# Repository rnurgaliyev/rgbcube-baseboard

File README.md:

# rgbcube-baseboard
BaseBoard design for RGB Cube Project

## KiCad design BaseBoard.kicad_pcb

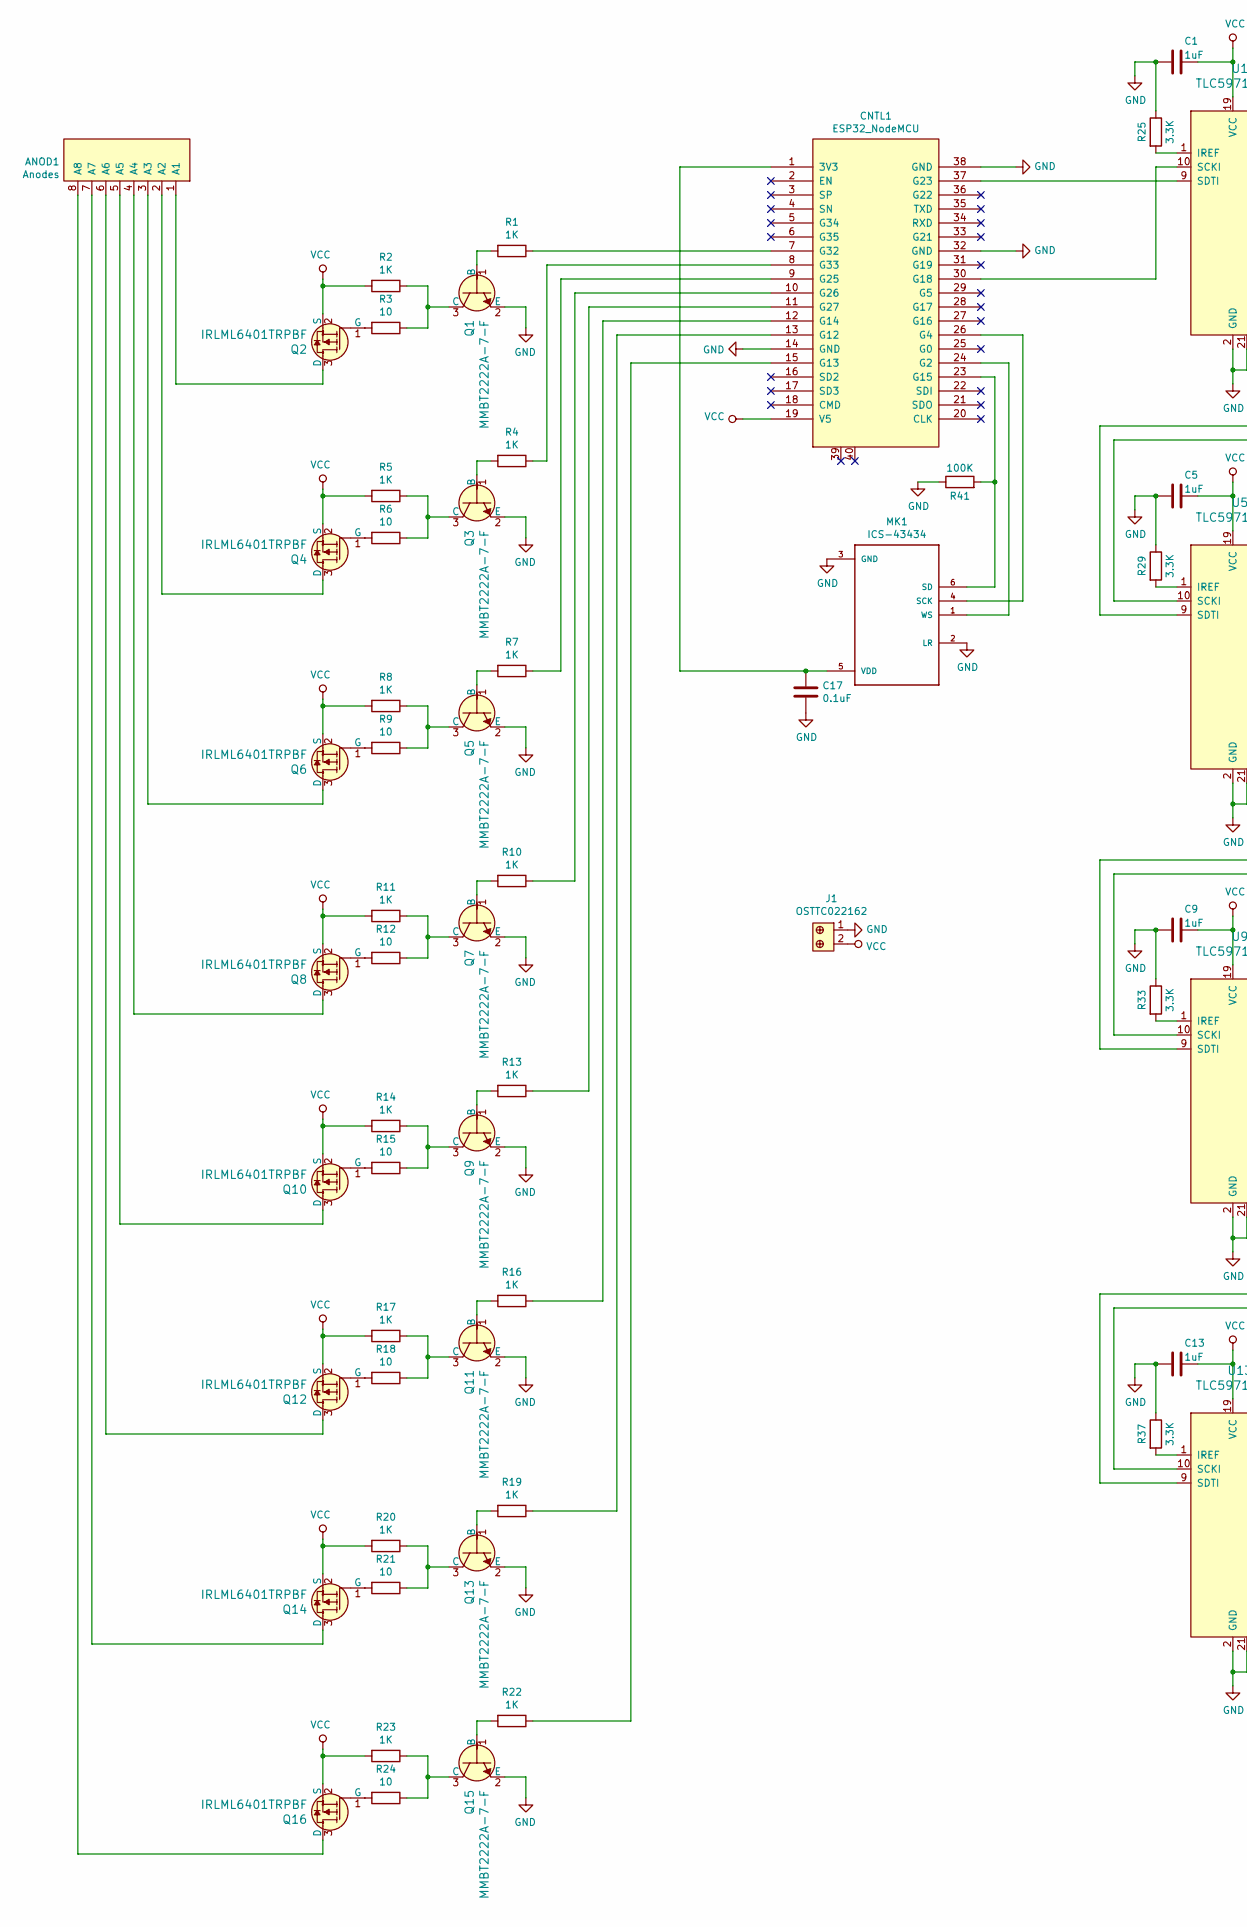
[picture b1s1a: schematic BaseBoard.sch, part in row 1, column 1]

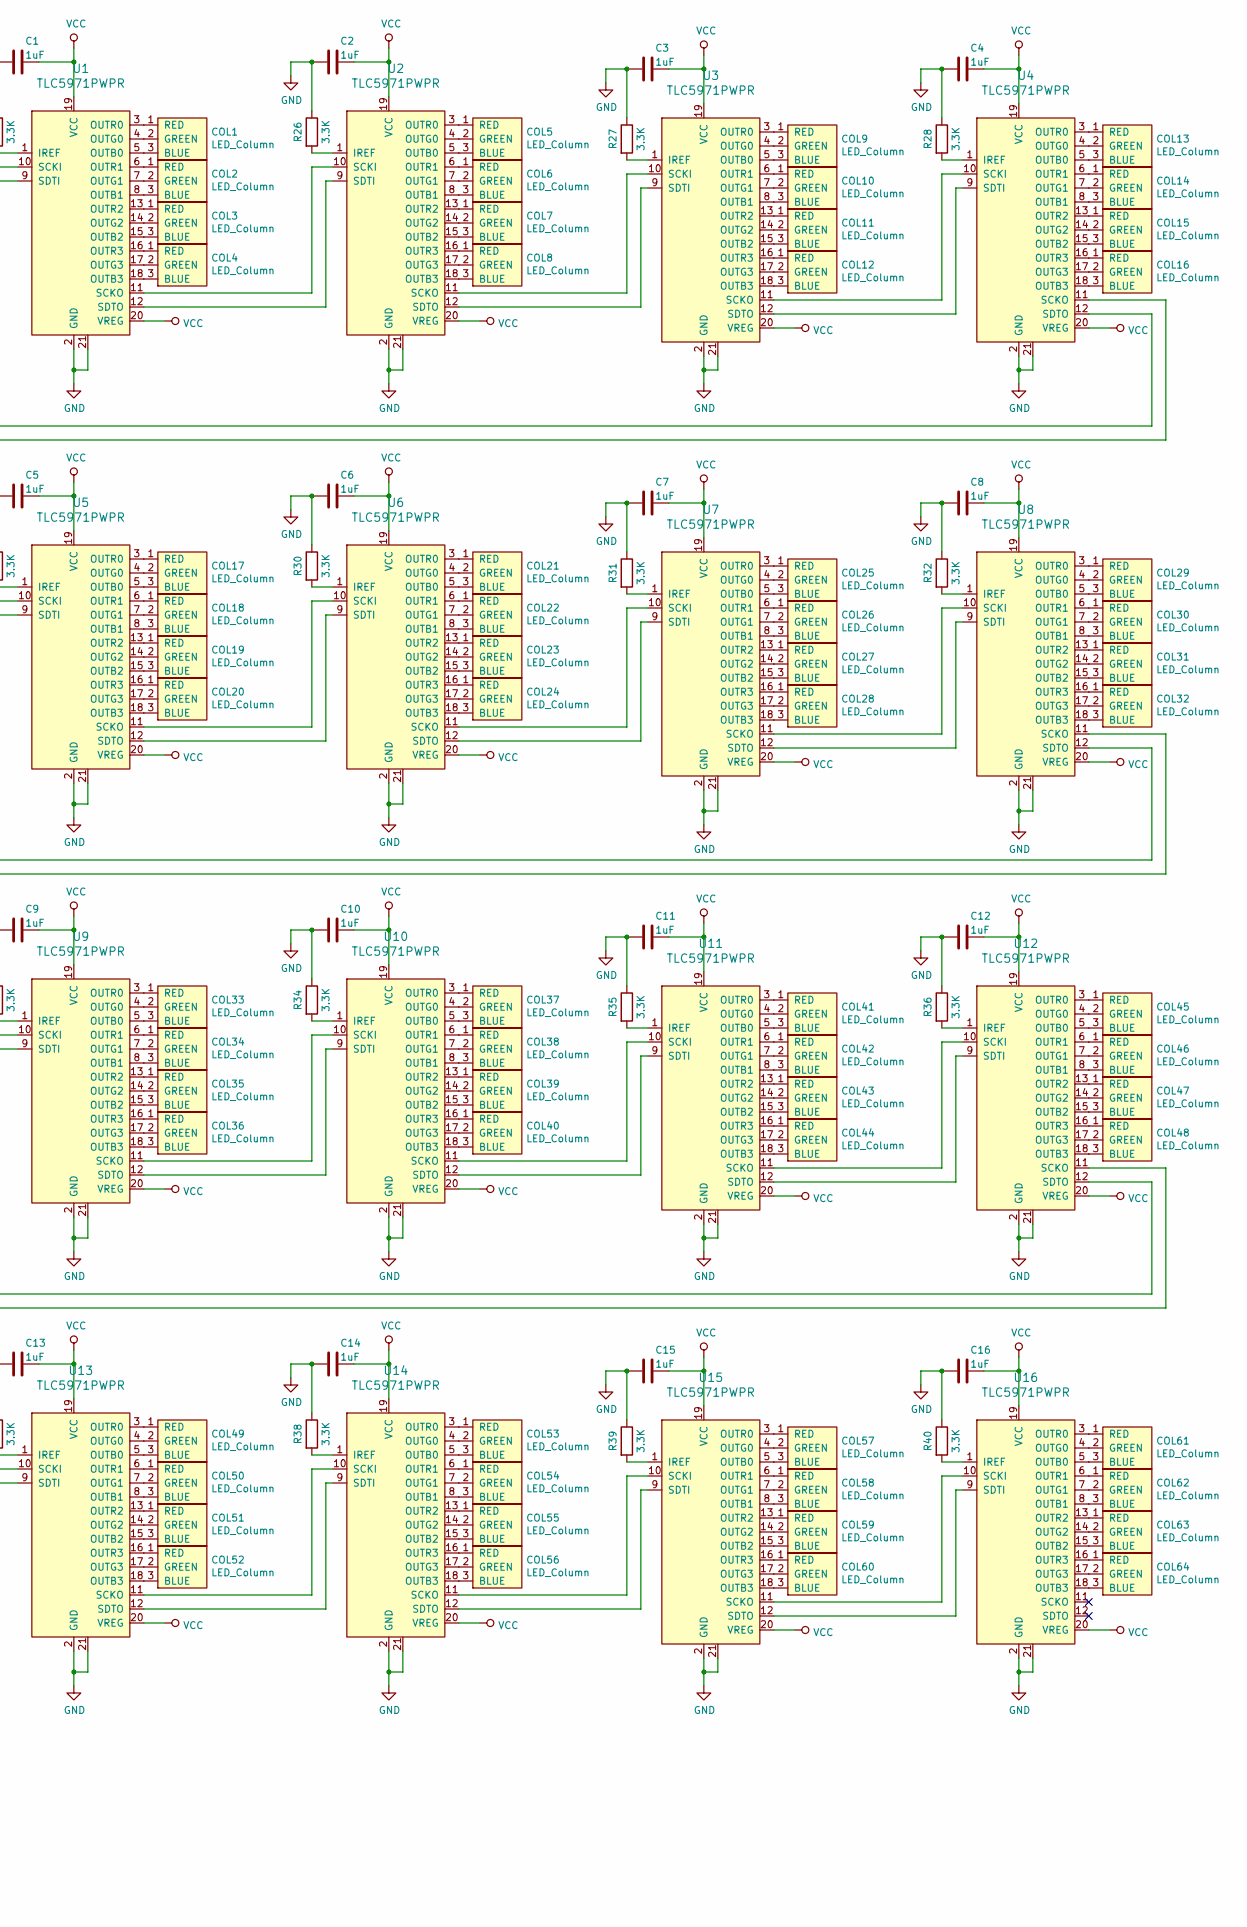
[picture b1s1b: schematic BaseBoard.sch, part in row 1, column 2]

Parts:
ANOD1: Anodes
C1, C2, C3, C4, C5, C6, C7, C8, C9, C10, C11, C12, C13, C14, C15, C16: 1uF; C_0805_2012Metric_Pad1.15x1.40mm_HandSolder
C17: 0.1uF; C_0805_2012Metric_Pad1.15x1.40mm_HandSolder
CNTL1: ESP32_NodeMCU
COL1, COL2, COL3, COL4, COL5, COL6, COL7, COL8, COL9, COL10, COL11, COL12, COL13, COL14, COL15, COL16, COL17, COL18, COL19, COL20, COL21, COL22, COL23, COL24, COL25, COL26, COL27, COL28, COL29, COL30, COL31, COL32, COL33, COL34, COL35, COL36, COL37, COL38, COL39, COL40, COL41, COL42, COL43, COL44, COL45, COL46, COL47, COL48, COL49, COL50, COL51, COL52, COL53, COL54, COL55, COL56, COL57, COL58, COL59, COL60, COL61, COL62, COL63, COL64: LED_Column
J1: OSTTC022162; Term_Block_1x2_P5.08MM; MPN OSTTC022162; Digi-Key_PN ED2609-ND
MK1: ICS-43434; MIC_ICS-43434
Q1, Q3, Q5, Q7, Q9, Q11, Q13, Q15: MMBT2222A-7-F; SOT-23-3; MPN MMBT2222A-7-F; Digi-Key_PN MMBT2222A-FDICT-ND
Q2, Q4, Q6, Q8, Q10, Q12, Q14, Q16: IRLML6401TRPBF; SOT-23-3; MPN IRLML6401TRPBF; Digi-Key_PN IRLML6401PBFCT-ND
R1, R2, R4, R5, R7, R8, R10, R11, R13, R14, R16, R17, R19, R20, R22, R23: 1K; R_0805_2012Metric_Pad1.15x1.40mm_HandSolder
R3, R6, R9, R12, R15, R18, R21, R24: 10; R_0805_2012Metric_Pad1.15x1.40mm_HandSolder
R25, R26, R27, R28, R29, R30, R31, R32, R33, R34, R35, R36, R37, R38, R39, R40: 3.3K; R_0805_2012Metric_Pad1.15x1.40mm_HandSolder
R41: 100K; R_0805_2012Metric_Pad1.15x1.40mm_HandSolder
U1, U2, U3, U4, U5, U6, U7, U8, U9, U10, U11, U12, U13, U14, U15, U16: TLC5971PWPR; HTSSOP-20-1EP_4.4x6.5mm_P0.65mm_EP3.4x6.5mm_Mask2.75x3.43mm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; MPN TLC5971PWPR; Digi-Key_PN 296-27796-1-ND

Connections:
GND: C1.1, C2.1, C3.1, C4.1, C5.1, C6.1, C7.1, C8.1, C9.1, C10.1, C11.1, C12.1, C13.1, C14.1, C15.1, C16.1, C17.2, CNTL1.14 (GND), CNTL1.32 (GND), CNTL1.38 (GND), J1.1, MK1.2 (LR), MK1.3 (GND), Q1.2 (E), Q3.2 (E), Q5.2 (E), Q7.2 (E), Q9.2 (E), Q11.2 (E), Q13.2 (E), Q15.2 (E), R25.1, R26.1, R27.1, R28.1, R29.1, R30.1, R31.1, R32.1, R33.1, R34.1, R35.1, R36.1, R37.1, R38.1, R39.1, R40.1, R41.1, U1.2 (GND), U1.21, U2.2 (GND), U2.21, U3.2 (GND), U3.21, U4.2 (GND), U4.21, U5.2 (GND), U5.21, U6.2 (GND), U6.21, U7.2 (GND), U7.21, U8.2 (GND), U8.21, U9.2 (GND), U9.21, U10.2 (GND), U10.21, U11.2 (GND), U11.21, U12.2 (GND), U12.21, U13.2 (GND), U13.21, U14.2 (GND), U14.21, U15.2 (GND), U15.21, U16.2 (GND), U16.21
unnamed: ANOD1.1 (A1), Q2.3 (D)
unnamed: ANOD1.2 (A2), Q4.3 (D)
unnamed: ANOD1.3 (A3), Q6.3 (D)
unnamed: ANOD1.4 (A4), Q8.3 (D)
unnamed: ANOD1.5 (A5), Q10.3 (D)
unnamed: ANOD1.6 (A6), Q12.3 (D)
unnamed: ANOD1.7 (A7), Q14.3 (D)
unnamed: ANOD1.8 (A8), Q16.3 (D)
unnamed: C17.1, CNTL1.1 (3V3), MK1.5 (VDD)
unnamed: CNTL1.7 (G32), R1.1
unnamed: CNTL1.8 (G33), R4.1
unnamed: CNTL1.9 (G25), R7.1
unnamed: CNTL1.10 (G26), R10.1
unnamed: CNTL1.11 (G27), R13.1
unnamed: CNTL1.12 (G14), R16.1
unnamed: CNTL1.13 (G12), R19.1
unnamed: CNTL1.15 (G13), R22.1
unnamed: CNTL1.23 (G15), MK1.6 (SD), R41.2
unnamed: CNTL1.24 (G2), MK1.1 (WS)
unnamed: CNTL1.26 (G4), MK1.4 (SCK)
unnamed: CNTL1.30 (G18), U1.10 (SCKI)
unnamed: CNTL1.37 (G23), U1.9 (SDTI)
unnamed: COL1.1 (RED), U1.3 (OUTR0)
unnamed: COL1.2 (GREEN), U1.4 (OUTG0)
unnamed: COL1.3 (BLUE), U1.5 (OUTB0)
unnamed: COL2.1 (RED), U1.6 (OUTR1)
unnamed: COL2.2 (GREEN), U1.7 (OUTG1)
unnamed: COL2.3 (BLUE), U1.8 (OUTB1)
unnamed: COL3.1 (RED), U1.13 (OUTR2)
unnamed: COL3.2 (GREEN), U1.14 (OUTG2)
unnamed: COL3.3 (BLUE), U1.15 (OUTB2)
unnamed: COL4.1 (RED), U1.16 (OUTR3)
unnamed: COL4.2 (GREEN), U1.17 (OUTG3)
unnamed: COL4.3 (BLUE), U1.18 (OUTB3)
unnamed: COL5.1 (RED), U2.3 (OUTR0)
unnamed: COL5.2 (GREEN), U2.4 (OUTG0)
unnamed: COL5.3 (BLUE), U2.5 (OUTB0)
unnamed: COL6.1 (RED), U2.6 (OUTR1)
unnamed: COL6.2 (GREEN), U2.7 (OUTG1)
unnamed: COL6.3 (BLUE), U2.8 (OUTB1)
unnamed: COL7.1 (RED), U2.13 (OUTR2)
unnamed: COL7.2 (GREEN), U2.14 (OUTG2)
unnamed: COL7.3 (BLUE), U2.15 (OUTB2)
unnamed: COL8.1 (RED), U2.16 (OUTR3)
unnamed: COL8.2 (GREEN), U2.17 (OUTG3)
unnamed: COL8.3 (BLUE), U2.18 (OUTB3)
unnamed: COL9.1 (RED), U3.3 (OUTR0)
unnamed: COL9.2 (GREEN), U3.4 (OUTG0)
unnamed: COL9.3 (BLUE), U3.5 (OUTB0)
unnamed: COL10.1 (RED), U3.6 (OUTR1)
unnamed: COL10.2 (GREEN), U3.7 (OUTG1)
unnamed: COL10.3 (BLUE), U3.8 (OUTB1)
unnamed: COL11.1 (RED), U3.13 (OUTR2)
unnamed: COL11.2 (GREEN), U3.14 (OUTG2)
unnamed: COL11.3 (BLUE), U3.15 (OUTB2)
unnamed: COL12.1 (RED), U3.16 (OUTR3)
unnamed: COL12.2 (GREEN), U3.17 (OUTG3)
unnamed: COL12.3 (BLUE), U3.18 (OUTB3)
unnamed: COL13.1 (RED), U4.3 (OUTR0)
unnamed: COL13.2 (GREEN), U4.4 (OUTG0)
unnamed: COL13.3 (BLUE), U4.5 (OUTB0)
unnamed: COL14.1 (RED), U4.6 (OUTR1)
unnamed: COL14.2 (GREEN), U4.7 (OUTG1)
unnamed: COL14.3 (BLUE), U4.8 (OUTB1)
unnamed: COL15.1 (RED), U4.13 (OUTR2)
unnamed: COL15.2 (GREEN), U4.14 (OUTG2)
unnamed: COL15.3 (BLUE), U4.15 (OUTB2)
unnamed: COL16.1 (RED), U4.16 (OUTR3)
unnamed: COL16.2 (GREEN), U4.17 (OUTG3)
unnamed: COL16.3 (BLUE), U4.18 (OUTB3)
unnamed: COL17.1 (RED), U5.3 (OUTR0)
unnamed: COL17.2 (GREEN), U5.4 (OUTG0)
unnamed: COL17.3 (BLUE), U5.5 (OUTB0)
unnamed: COL18.1 (RED), U5.6 (OUTR1)
unnamed: COL18.2 (GREEN), U5.7 (OUTG1)
unnamed: COL18.3 (BLUE), U5.8 (OUTB1)
unnamed: COL19.1 (RED), U5.13 (OUTR2)
unnamed: COL19.2 (GREEN), U5.14 (OUTG2)
unnamed: COL19.3 (BLUE), U5.15 (OUTB2)
unnamed: COL20.1 (RED), U5.16 (OUTR3)
unnamed: COL20.2 (GREEN), U5.17 (OUTG3)
unnamed: COL20.3 (BLUE), U5.18 (OUTB3)
unnamed: COL21.1 (RED), U6.3 (OUTR0)
unnamed: COL21.2 (GREEN), U6.4 (OUTG0)
unnamed: COL21.3 (BLUE), U6.5 (OUTB0)
unnamed: COL22.1 (RED), U6.6 (OUTR1)
unnamed: COL22.2 (GREEN), U6.7 (OUTG1)
unnamed: COL22.3 (BLUE), U6.8 (OUTB1)
unnamed: COL23.1 (RED), U6.13 (OUTR2)
unnamed: COL23.2 (GREEN), U6.14 (OUTG2)
unnamed: COL23.3 (BLUE), U6.15 (OUTB2)
unnamed: COL24.1 (RED), U6.16 (OUTR3)
unnamed: COL24.2 (GREEN), U6.17 (OUTG3)
unnamed: COL24.3 (BLUE), U6.18 (OUTB3)
unnamed: COL25.1 (RED), U7.3 (OUTR0)
unnamed: COL25.2 (GREEN), U7.4 (OUTG0)
unnamed: COL25.3 (BLUE), U7.5 (OUTB0)
unnamed: COL26.1 (RED), U7.6 (OUTR1)
unnamed: COL26.2 (GREEN), U7.7 (OUTG1)
unnamed: COL26.3 (BLUE), U7.8 (OUTB1)
unnamed: COL27.1 (RED), U7.13 (OUTR2)
unnamed: COL27.2 (GREEN), U7.14 (OUTG2)
unnamed: COL27.3 (BLUE), U7.15 (OUTB2)
unnamed: COL28.1 (RED), U7.16 (OUTR3)
unnamed: COL28.2 (GREEN), U7.17 (OUTG3)
unnamed: COL28.3 (BLUE), U7.18 (OUTB3)
unnamed: COL29.1 (RED), U8.3 (OUTR0)
unnamed: COL29.2 (GREEN), U8.4 (OUTG0)
unnamed: COL29.3 (BLUE), U8.5 (OUTB0)
unnamed: COL30.1 (RED), U8.6 (OUTR1)
unnamed: COL30.2 (GREEN), U8.7 (OUTG1)
unnamed: COL30.3 (BLUE), U8.8 (OUTB1)
unnamed: COL31.1 (RED), U8.13 (OUTR2)
unnamed: COL31.2 (GREEN), U8.14 (OUTG2)
unnamed: COL31.3 (BLUE), U8.15 (OUTB2)
unnamed: COL32.1 (RED), U8.16 (OUTR3)
unnamed: COL32.2 (GREEN), U8.17 (OUTG3)
unnamed: COL32.3 (BLUE), U8.18 (OUTB3)
unnamed: COL33.1 (RED), U9.3 (OUTR0)
unnamed: COL33.2 (GREEN), U9.4 (OUTG0)
unnamed: COL33.3 (BLUE), U9.5 (OUTB0)
unnamed: COL34.1 (RED), U9.6 (OUTR1)
unnamed: COL34.2 (GREEN), U9.7 (OUTG1)
unnamed: COL34.3 (BLUE), U9.8 (OUTB1)
unnamed: COL35.1 (RED), U9.13 (OUTR2)
unnamed: COL35.2 (GREEN), U9.14 (OUTG2)
unnamed: COL35.3 (BLUE), U9.15 (OUTB2)
unnamed: COL36.1 (RED), U9.16 (OUTR3)
unnamed: COL36.2 (GREEN), U9.17 (OUTG3)
unnamed: COL36.3 (BLUE), U9.18 (OUTB3)
unnamed: COL37.1 (RED), U10.3 (OUTR0)
unnamed: COL37.2 (GREEN), U10.4 (OUTG0)
unnamed: COL37.3 (BLUE), U10.5 (OUTB0)
unnamed: COL38.1 (RED), U10.6 (OUTR1)
unnamed: COL38.2 (GREEN), U10.7 (OUTG1)
unnamed: COL38.3 (BLUE), U10.8 (OUTB1)
unnamed: COL39.1 (RED), U10.13 (OUTR2)
unnamed: COL39.2 (GREEN), U10.14 (OUTG2)
unnamed: COL39.3 (BLUE), U10.15 (OUTB2)
unnamed: COL40.1 (RED), U10.16 (OUTR3)
unnamed: COL40.2 (GREEN), U10.17 (OUTG3)
unnamed: COL40.3 (BLUE), U10.18 (OUTB3)
unnamed: COL41.1 (RED), U11.3 (OUTR0)
unnamed: COL41.2 (GREEN), U11.4 (OUTG0)
unnamed: COL41.3 (BLUE), U11.5 (OUTB0)
unnamed: COL42.1 (RED), U11.6 (OUTR1)
unnamed: COL42.2 (GREEN), U11.7 (OUTG1)
unnamed: COL42.3 (BLUE), U11.8 (OUTB1)
unnamed: COL43.1 (RED), U11.13 (OUTR2)
unnamed: COL43.2 (GREEN), U11.14 (OUTG2)
unnamed: COL43.3 (BLUE), U11.15 (OUTB2)
unnamed: COL44.1 (RED), U11.16 (OUTR3)
unnamed: COL44.2 (GREEN), U11.17 (OUTG3)
unnamed: COL44.3 (BLUE), U11.18 (OUTB3)
unnamed: COL45.1 (RED), U12.3 (OUTR0)
unnamed: COL45.2 (GREEN), U12.4 (OUTG0)
unnamed: COL45.3 (BLUE), U12.5 (OUTB0)
unnamed: COL46.1 (RED), U12.6 (OUTR1)
unnamed: COL46.2 (GREEN), U12.7 (OUTG1)
unnamed: COL46.3 (BLUE), U12.8 (OUTB1)
unnamed: COL47.1 (RED), U12.13 (OUTR2)
unnamed: COL47.2 (GREEN), U12.14 (OUTG2)
unnamed: COL47.3 (BLUE), U12.15 (OUTB2)
unnamed: COL48.1 (RED), U12.16 (OUTR3)
unnamed: COL48.2 (GREEN), U12.17 (OUTG3)
unnamed: COL48.3 (BLUE), U12.18 (OUTB3)
unnamed: COL49.1 (RED), U13.3 (OUTR0)
unnamed: COL49.2 (GREEN), U13.4 (OUTG0)
unnamed: COL49.3 (BLUE), U13.5 (OUTB0)
unnamed: COL50.1 (RED), U13.6 (OUTR1)
unnamed: COL50.2 (GREEN), U13.7 (OUTG1)
unnamed: COL50.3 (BLUE), U13.8 (OUTB1)
unnamed: COL51.1 (RED), U13.13 (OUTR2)
unnamed: COL51.2 (GREEN), U13.14 (OUTG2)
unnamed: COL51.3 (BLUE), U13.15 (OUTB2)
unnamed: COL52.1 (RED), U13.16 (OUTR3)
unnamed: COL52.2 (GREEN), U13.17 (OUTG3)
unnamed: COL52.3 (BLUE), U13.18 (OUTB3)
unnamed: COL53.1 (RED), U14.3 (OUTR0)
unnamed: COL53.2 (GREEN), U14.4 (OUTG0)
unnamed: COL53.3 (BLUE), U14.5 (OUTB0)
unnamed: COL54.1 (RED), U14.6 (OUTR1)
unnamed: COL54.2 (GREEN), U14.7 (OUTG1)
unnamed: COL54.3 (BLUE), U14.8 (OUTB1)
unnamed: COL55.1 (RED), U14.13 (OUTR2)
unnamed: COL55.2 (GREEN), U14.14 (OUTG2)
unnamed: COL55.3 (BLUE), U14.15 (OUTB2)
unnamed: COL56.1 (RED), U14.16 (OUTR3)
unnamed: COL56.2 (GREEN), U14.17 (OUTG3)
unnamed: COL56.3 (BLUE), U14.18 (OUTB3)
unnamed: COL57.1 (RED), U15.3 (OUTR0)
unnamed: COL57.2 (GREEN), U15.4 (OUTG0)
unnamed: COL57.3 (BLUE), U15.5 (OUTB0)
unnamed: COL58.1 (RED), U15.6 (OUTR1)
unnamed: COL58.2 (GREEN), U15.7 (OUTG1)
unnamed: COL58.3 (BLUE), U15.8 (OUTB1)
unnamed: COL59.1 (RED), U15.13 (OUTR2)
unnamed: COL59.2 (GREEN), U15.14 (OUTG2)
unnamed: COL59.3 (BLUE), U15.15 (OUTB2)
unnamed: COL60.1 (RED), U15.16 (OUTR3)
unnamed: COL60.2 (GREEN), U15.17 (OUTG3)
unnamed: COL60.3 (BLUE), U15.18 (OUTB3)
unnamed: COL61.1 (RED), U16.3 (OUTR0)
unnamed: COL61.2 (GREEN), U16.4 (OUTG0)
unnamed: COL61.3 (BLUE), U16.5 (OUTB0)
unnamed: COL62.1 (RED), U16.6 (OUTR1)
unnamed: COL62.2 (GREEN), U16.7 (OUTG1)
unnamed: COL62.3 (BLUE), U16.8 (OUTB1)
unnamed: COL63.1 (RED), U16.13 (OUTR2)
unnamed: COL63.2 (GREEN), U16.14 (OUTG2)
unnamed: COL63.3 (BLUE), U16.15 (OUTB2)
unnamed: COL64.1 (RED), U16.16 (OUTR3)
unnamed: COL64.2 (GREEN), U16.17 (OUTG3)
unnamed: COL64.3 (BLUE), U16.18 (OUTB3)
unnamed: Q1.1 (B), R1.2
unnamed: Q1.3 (C), R2.1, R3.1
unnamed: Q2.1 (G), R3.2
unnamed: Q3.1 (B), R4.2
unnamed: Q3.3 (C), R5.1, R6.1
unnamed: Q4.1 (G), R6.2
unnamed: Q5.1 (B), R7.2
unnamed: Q5.3 (C), R8.1, R9.1
unnamed: Q6.1 (G), R9.2
unnamed: Q7.1 (B), R10.2
unnamed: Q7.3 (C), R11.1, R12.1
unnamed: Q8.1 (G), R12.2
unnamed: Q9.1 (B), R13.2
unnamed: Q9.3 (C), R14.1, R15.1
unnamed: Q10.1 (G), R15.2
unnamed: Q11.1 (B), R16.2
unnamed: Q11.3 (C), R17.1, R18.1
unnamed: Q12.1 (G), R18.2
unnamed: Q13.1 (B), R19.2
unnamed: Q13.3 (C), R20.1, R21.1
unnamed: Q14.1 (G), R21.2
unnamed: Q15.1 (B), R22.2
unnamed: Q15.3 (C), R23.1, R24.1
unnamed: Q16.1 (G), R24.2
unnamed: R25.2, U1.1 (IREF)
unnamed: R26.2, U2.1 (IREF)
unnamed: R27.2, U3.1 (IREF)
unnamed: R28.2, U4.1 (IREF)
unnamed: R29.2, U5.1 (IREF)
unnamed: R30.2, U6.1 (IREF)
unnamed: R31.2, U7.1 (IREF)
unnamed: R32.2, U8.1 (IREF)
unnamed: R33.2, U9.1 (IREF)
unnamed: R34.2, U10.1 (IREF)
unnamed: R35.2, U11.1 (IREF)
unnamed: R36.2, U12.1 (IREF)
unnamed: R37.2, U13.1 (IREF)
unnamed: R38.2, U14.1 (IREF)
unnamed: R39.2, U15.1 (IREF)
unnamed: R40.2, U16.1 (IREF)
unnamed: U1.11 (SCKO), U2.10 (SCKI)
unnamed: U1.12 (SDTO), U2.9 (SDTI)
unnamed: U2.11 (SCKO), U3.10 (SCKI)
unnamed: U2.12 (SDTO), U3.9 (SDTI)
unnamed: U3.11 (SCKO), U4.10 (SCKI)
unnamed: U3.12 (SDTO), U4.9 (SDTI)
unnamed: U4.11 (SCKO), U5.10 (SCKI)
unnamed: U4.12 (SDTO), U5.9 (SDTI)
unnamed: U5.11 (SCKO), U6.10 (SCKI)
unnamed: U5.12 (SDTO), U6.9 (SDTI)
unnamed: U6.11 (SCKO), U7.10 (SCKI)
unnamed: U6.12 (SDTO), U7.9 (SDTI)
unnamed: U7.11 (SCKO), U8.10 (SCKI)
unnamed: U7.12 (SDTO), U8.9 (SDTI)
unnamed: U8.11 (SCKO), U9.10 (SCKI)
unnamed: U8.12 (SDTO), U9.9 (SDTI)
unnamed: U9.12 (SDTO), U10.9 (SDTI)
unnamed: U9.11 (SCKO), U10.10 (SCKI)
unnamed: U10.11 (SCKO), U11.10 (SCKI)
unnamed: U10.12 (SDTO), U11.9 (SDTI)
unnamed: U11.11 (SCKO), U12.10 (SCKI)
unnamed: U11.12 (SDTO), U12.9 (SDTI)
unnamed: U12.11 (SCKO), U13.10 (SCKI)
unnamed: U12.12 (SDTO), U13.9 (SDTI)
unnamed: U13.11 (SCKO), U14.10 (SCKI)
unnamed: U13.12 (SDTO), U14.9 (SDTI)
unnamed: U14.11 (SCKO), U15.10 (SCKI)
unnamed: U14.12 (SDTO), U15.9 (SDTI)
unnamed: U15.11 (SCKO), U16.10 (SCKI)
unnamed: U15.12 (SDTO), U16.9 (SDTI)
VCC: C1.2, C2.2, C3.2, C4.2, C5.2, C6.2, C7.2, C8.2, C9.2, C10.2, C11.2, C12.2, C13.2, C14.2, C15.2, C16.2, CNTL1.19 (V5), J1.2, Q2.2 (S), Q4.2 (S), Q6.2 (S), Q8.2 (S), Q10.2 (S), Q12.2 (S), Q14.2 (S), Q16.2 (S), R2.2, R5.2, R8.2, R11.2, R14.2, R17.2, R20.2, R23.2, U1.19 (VCC), U1.20 (VREG), U2.19 (VCC), U2.20 (VREG), U3.19 (VCC), U3.20 (VREG), U4.19 (VCC), U4.20 (VREG), U5.19 (VCC), U5.20 (VREG), U6.19 (VCC), U6.20 (VREG), U7.19 (VCC), U7.20 (VREG), U8.19 (VCC), U8.20 (VREG), U9.19 (VCC), U9.20 (VREG), U10.19 (VCC), U10.20 (VREG), U11.19 (VCC), U11.20 (VREG), U12.19 (VCC), U12.20 (VREG), U13.19 (VCC), U13.20 (VREG), U14.19 (VCC), U14.20 (VREG), U15.19 (VCC), U15.20 (VREG), U16.19 (VCC), U16.20 (VREG)

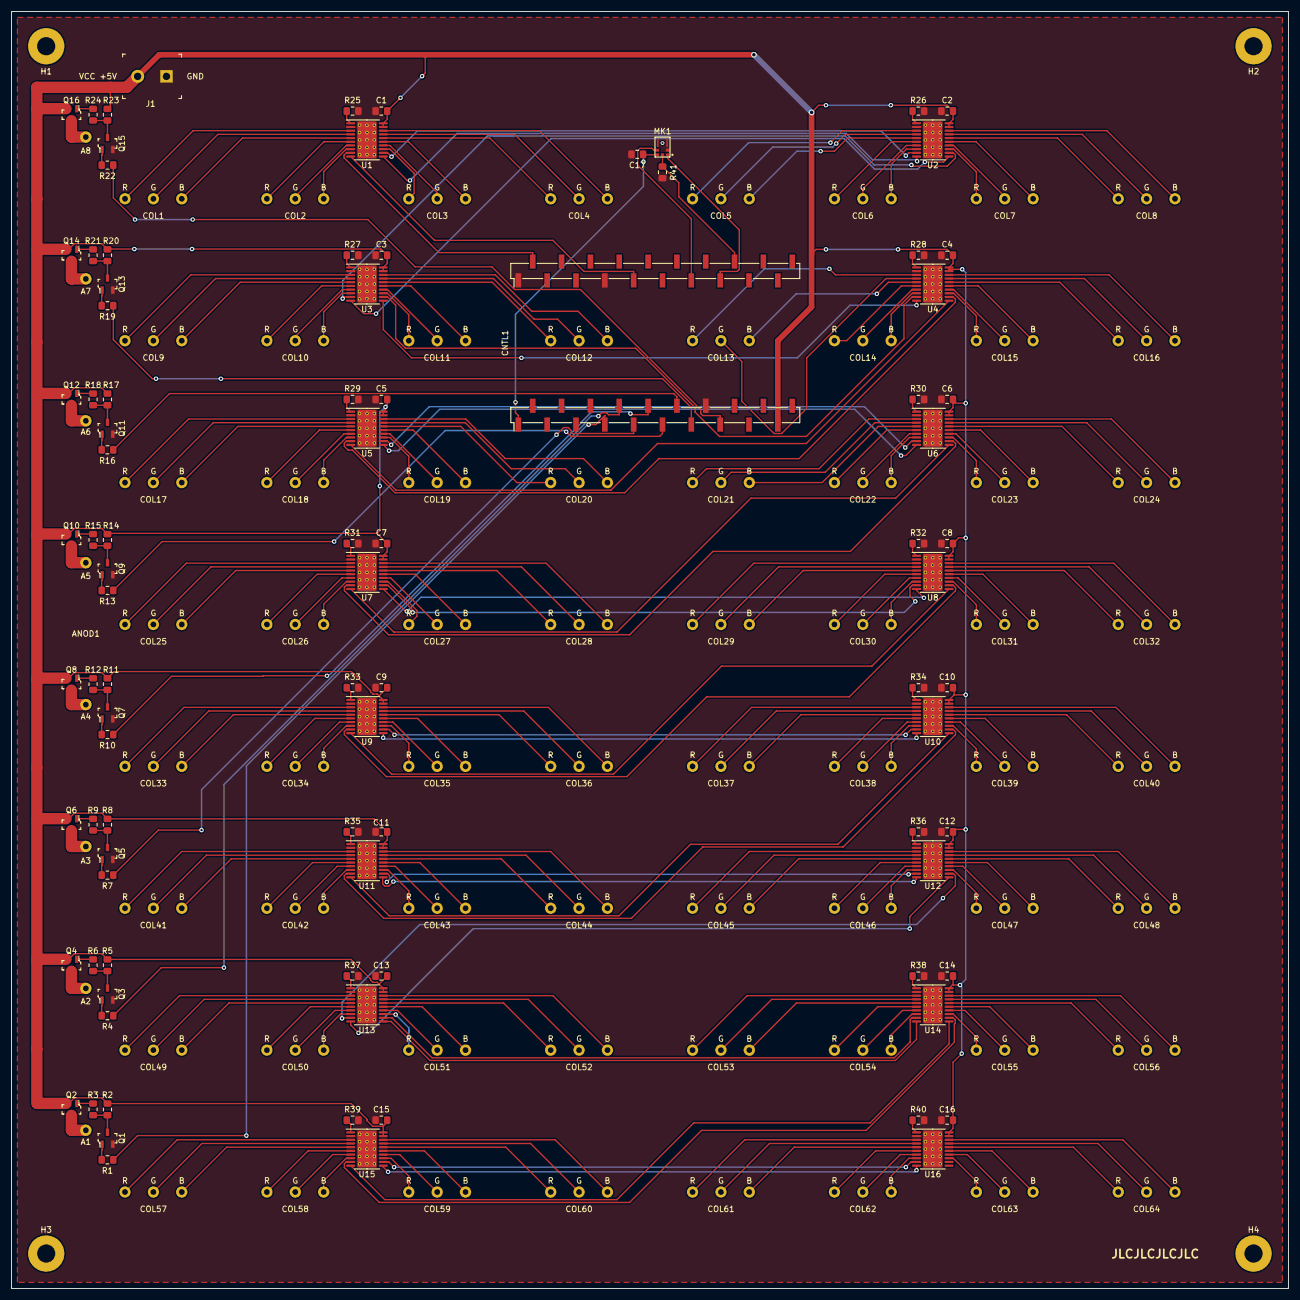
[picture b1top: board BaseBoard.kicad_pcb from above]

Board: 2 copper layers, 225.0 x 225.0 mm, 162 parts (0 on the bottom side), 286 nets.

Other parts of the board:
H1, H2, H3, H4: MountingHole_3.2mm_M3_Pad

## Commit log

2020-04-28 Add ESP32 footprint by @antonu17
2020-04-29 Add node-mcu component to library
2020-04-30 Reworked schematics
2020-04-30 Add anotations
2020-04-30 Add footprints to common components
2020-05-03 Fix lots of fuckups
2020-05-03 Add PCB base
2020-05-04 Before autorouting
2020-05-05 Update footprints
2020-05-05 Improve schematics and PCB
2020-05-11 Realign some components
2020-05-18 Add all routing
2020-06-04 Latest changes
2020-06-04 Add zone to back copper layer
